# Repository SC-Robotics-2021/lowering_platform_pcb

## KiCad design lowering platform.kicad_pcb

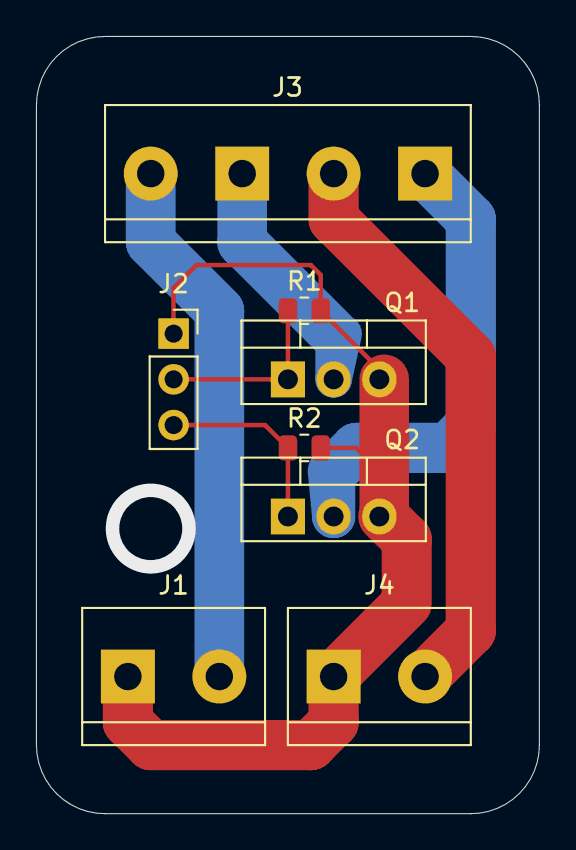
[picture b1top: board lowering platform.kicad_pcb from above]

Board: 2 copper layers, 27.9 x 43.2 mm, 8 parts (0 on the bottom side), 7 nets.

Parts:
J1, J4: Screw_Terminal_01x02; TerminalBlock_bornier-2_P5.08mm
J2: Conn_01x03_Female; PinSocket_1x03_P2.54mm_Vertical
J3: Screw_Terminal_01x04; TerminalBlock_bornier-4_P5.08mm
Q1, Q2: IRLB8721PBF; TO-220-3_Vertical
R1, R2: 10K; R_0805_2012Metric

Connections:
+5V: J3.3, J4.2
+12V: J1.2, J3.1
COM: J1.1, J2.1, J4.1, Q1.3, Q2.3, R1.2, R2.2
D_BRUSH: J3.2, Q1.2
D_LIGHT: J3.4, Q2.2
G_BRUSH: J2.2, Q1.1, R1.1
G_LIGHT: J2.3, Q2.1, R2.1

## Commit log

2022-05-02 Uploading Lowering Platform PCB
